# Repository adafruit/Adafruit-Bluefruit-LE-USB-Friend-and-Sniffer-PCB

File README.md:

## Adafruit Bluefruit LE USB Friend and Sniffer
&nbsp; <br />
Click to purchase from the Adafruit Shop:
- [Bluefruit LE Friend - Bluetooth Low Energy (BLE 4.0) - nRF51822 - v3.0](https://www.adafruit.com/product/2267)
- [Bluefruit LE Sniffer - Bluetooth Low Energy (BLE 4.0) - nRF51822 - Firmware Version 2](https://www.adafruit.com/product/2269)

The Bluefruit LE Friend is your new BLE BFF! This USB-to-BLE board makes it easy to get your computer talking to your BLE enabled phone or tablet using a standard serial/UART connection.

In it's simplest form, it works on the same principle as a common USB/Serial adapter (the FTDI Friend, for example!). Any data that you enter via your favorite terminal emulator on your development machine will be transferred over the air to the connected phone or tablet, and vice versa, as a basic 'UART' connection.

PCB files for the Bluefruit LE USB Friend and Sniffer
- https://www.adafruit.com/product/2267
- https://www.adafruit.com/product/2269

### License

Adafruit invests time and resources providing this open source design, please support Adafruit and open-source hardware by [purchasing products from Adafruit](https://www.adafruit.com)!

All text above must be included in any redistribution

Designed by Limor Fried/Ladyada for Adafruit Industries.
Creative Commons Attribution/Share-Alike, all text above must be included in any redistribution. 
See license.txt for additional information.

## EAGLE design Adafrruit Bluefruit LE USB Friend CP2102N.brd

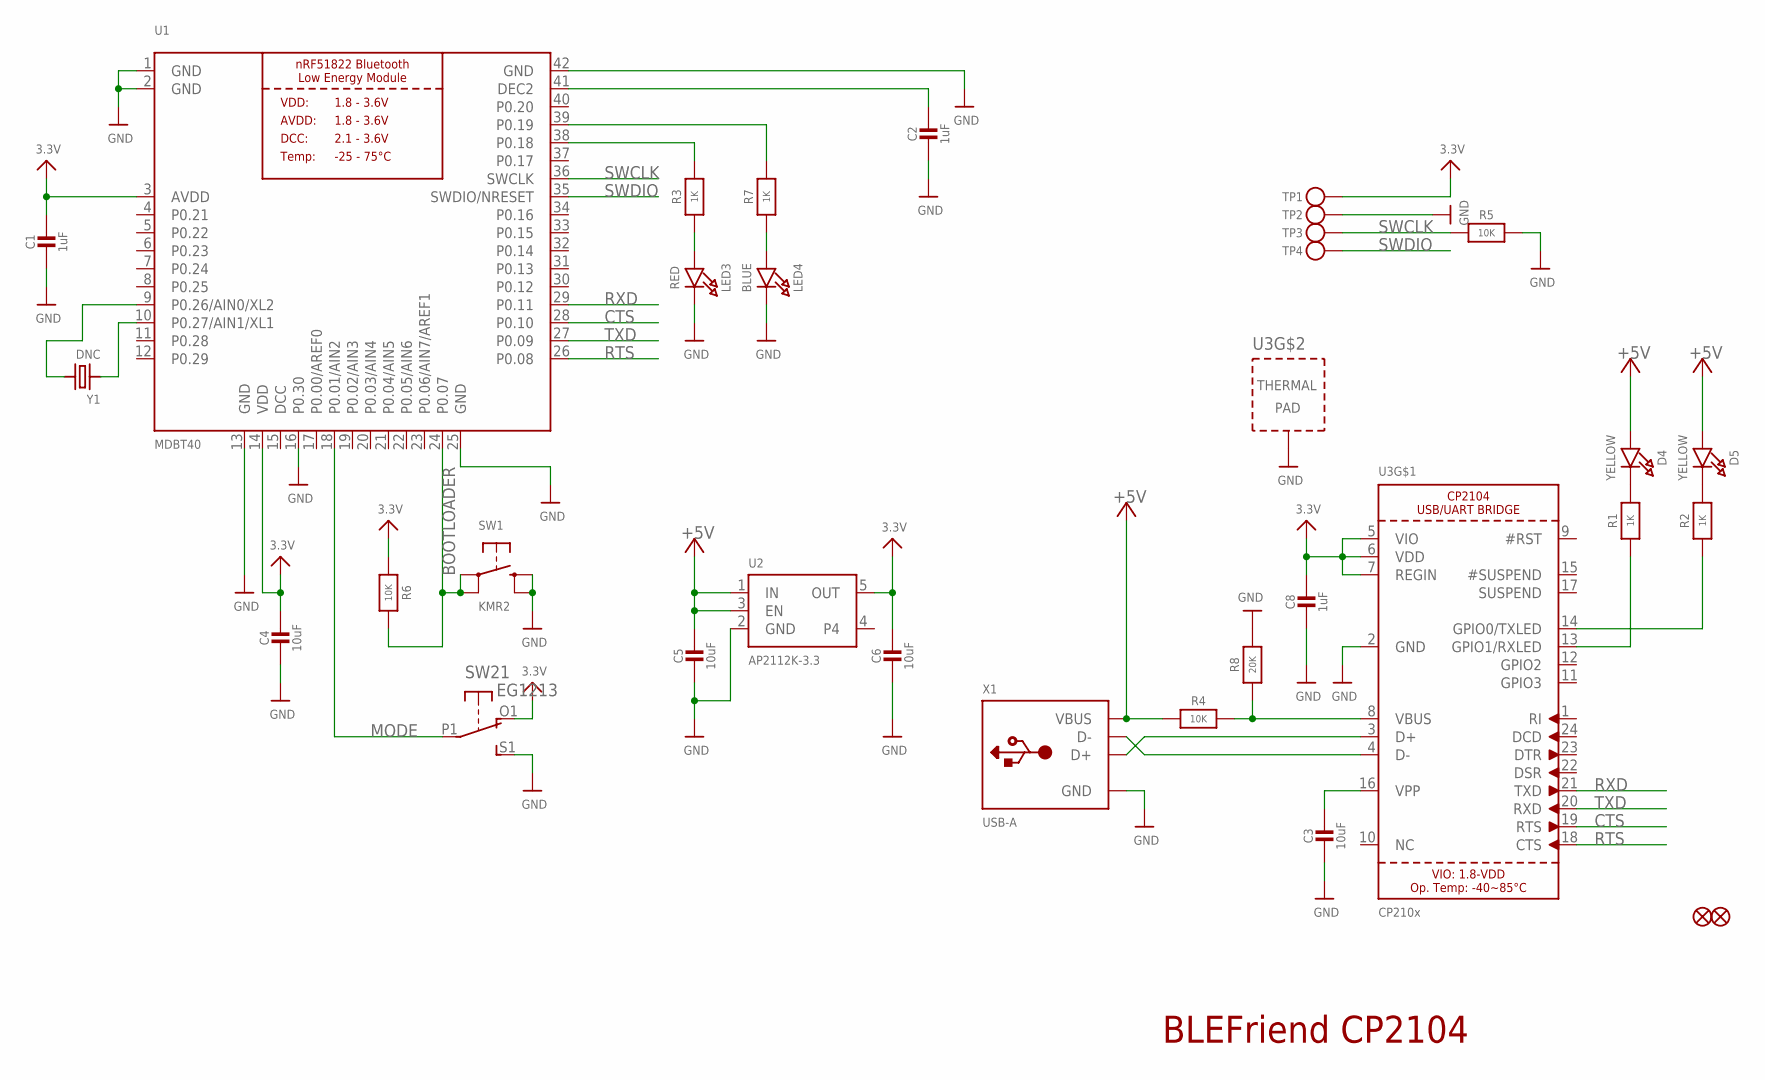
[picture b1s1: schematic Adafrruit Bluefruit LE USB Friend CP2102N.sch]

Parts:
C1, C2, C8: 1uF; 0603-NO
C3, C4, C5, C6: 10uF; 0805-NO
D4, D5: YELLOW; CHIPLED_0805_NOOUTLINE
FID1, FID2: FIDUCIAL_1MM
LED3: RED; CHIPLED_0805_NOOUTLINE
LED4: BLUE; CHIPLED_0805_NOOUTLINE
R1, R2, R3, R7: 1K; 0603-NO
R4, R5, R6: 10K; 0603-NO
R8: 20K; 0603-NO
SW1: KMR2; BTN_KMR2_4.6X2.8
SW2: EG1213; EG1390
TP1, TP2, TP3, TP4: TESTPOINTROUND2MM; TESTPOINT_ROUND_2MM
U1: MDBT40; BLE_MODULE_RAYTAC_MDBT40
U2: AP2112K-3.3; SOT23-5
U3: CP210x; QFN24_4MM_SMSC
X1: USB-A; USB_A-THM
Y1: DNC; CRYSTAL_CYL_2X6MM_SMT

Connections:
3.3V: C1.1, C4.1, C6.1, C8.1, R6.1, SW2.O1 (O), TP1.P$1, U1.3 (AVDD), U1.14 (VDD), U2.5 (OUT), U3.5 (VIO), U3.6 (VDD), U3.7 (REGIN)
+5V: C5.1, D4.A, D5.A, R4.1, U2.1 (IN), U2.3 (EN), X1.VBUS
BOOTLOADER: R6.2, SW1.A, SW1.A' (P1), U1.24 (P0.07)
CTS: U1.28 (P0.10), U3.19 (RTS)
DCC: U1.15 (DCC)
DEC2: C2.1, U1.41 (DEC2)
GND: C1.2, C2.2, C3.2, C4.2, C5.2, C6.2, C8.2, LED3.C, LED4.C, R5.2, R8.2, SW1.B (S), SW1.B' (S1), SW2.S1 (S), TP2.P$1, U1.1 (GND), U1.2 (GND), U1.13 (GND), U1.16 (P0.30), U1.25 (GND), U1.42 (GND), U2.2 (GND), U3.2 (GND), U3.THERM (TP), X1.GND
MODE: SW2.P1, U1.18 (P0.01/AIN2)
unnamed: U3.4 (D-), X1.D-
unnamed: D4.C, R1.2
unnamed: LED3.A, R3.1
unnamed: C3.1, U3.16 (VPP)
unnamed: R2.1, U3.14 (GPIO0/TXLED)
unnamed: D5.C, R2.2
unnamed: R4.2, R8.1, U3.8 (VBUS)
unnamed: U3.3 (D+), X1.D+
unnamed: R3.2, U1.38 (P0.18)
unnamed: R7.2, U1.39 (P0.19)
unnamed: LED4.A, R7.1
unnamed: U1.9 (P0.26/AIN0/XL2), Y1.2
unnamed: U1.10 (P0.27/AIN1/XL1), Y1.1
unnamed: R1.1, U3.13 (GPIO1/RXLED)
RTS: U1.26 (P0.08), U3.18 (CTS)
RXD: U1.29 (P0.11), U3.21 (TXD)
SWCLK: R5.1, TP3.P$1, U1.36 (SWCLK)
SWDIO: TP4.P$1, U1.35 (SWDIO/NRESET)
TXD: U1.27 (P0.09), U3.20 (RXD)

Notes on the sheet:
BLEFriend CP2104

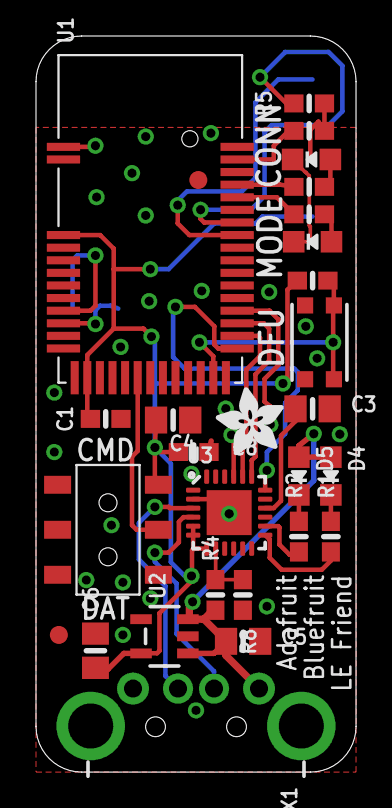
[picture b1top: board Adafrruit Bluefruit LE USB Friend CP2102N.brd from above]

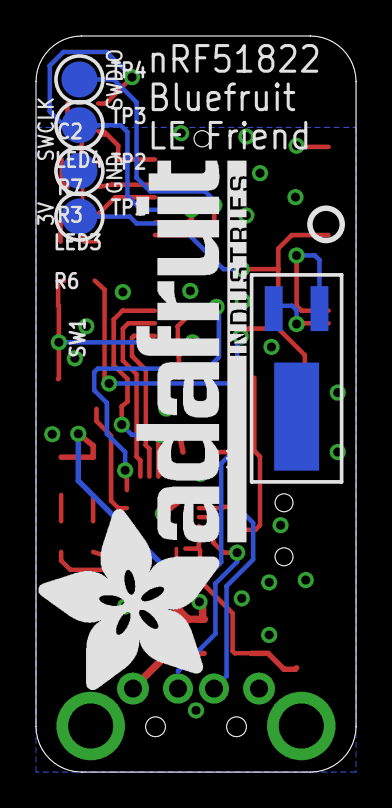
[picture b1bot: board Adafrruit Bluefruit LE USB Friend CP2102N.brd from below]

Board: 2 copper layers, 17.8 x 40.9 mm, 35 parts (7 on the bottom side), 26 nets.

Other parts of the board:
U$16: PCBFEAT-REV-040
U$22: ADAFRUIT_TEXT_30MM
U$31: ADAFRUIT_3.5MM

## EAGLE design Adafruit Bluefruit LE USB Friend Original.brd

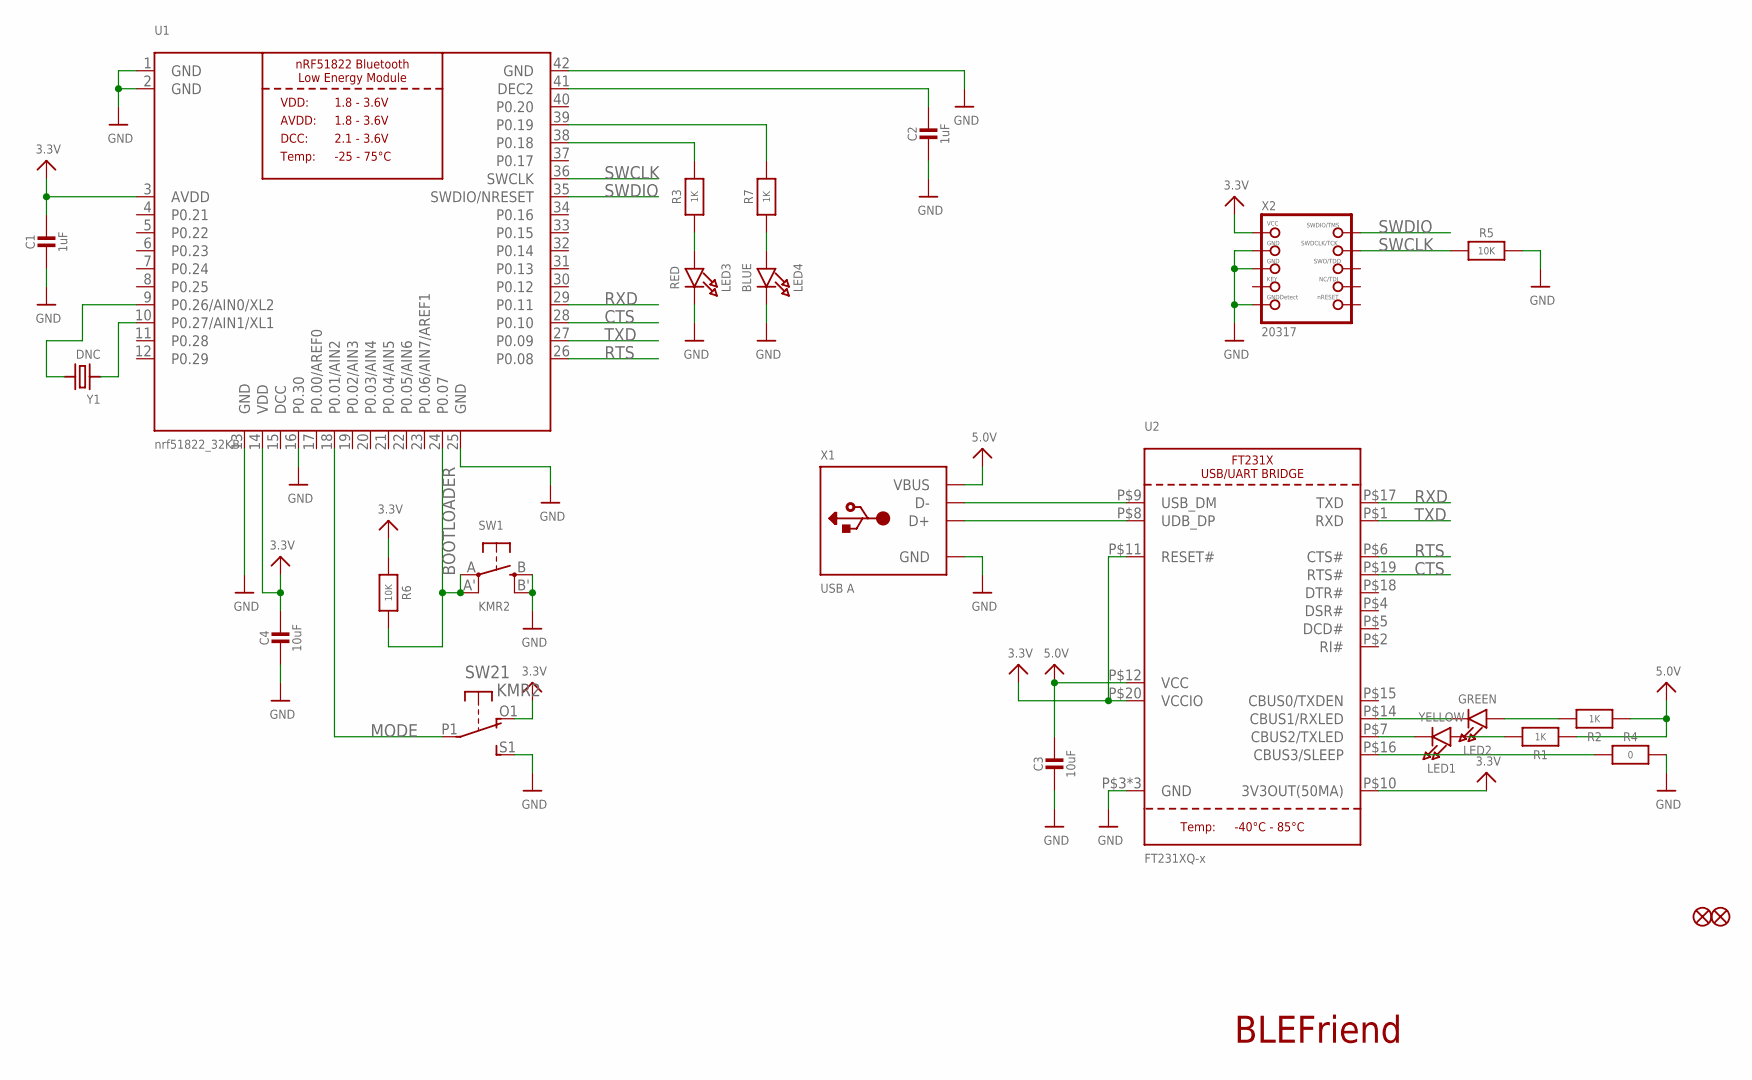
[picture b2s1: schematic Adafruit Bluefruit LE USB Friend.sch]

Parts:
C1, C2: 1uF; _0805MP
C3, C4: 10uF; _0805MP
FID1, FID2: FIDUCIAL""; FIDUCIAL_1MM
LED1: YELLOW; CHIPLED_0805_NOOUTLINE
LED2: GREEN; CHIPLED_0805_NOOUTLINE
LED3: RED; CHIPLED_0805_NOOUTLINE
LED4: BLUE; CHIPLED_0805_NOOUTLINE
R1, R2, R3, R7: 1K; _0805MP
R4: 0; _0805MP
R5, R6: 10K; _0805MP
SW1: KMR2; BTN_KMR2_4.6X2.8
SW2: KMR2; EG1390
U1: nrf51822_32KB; BLE_MODULE_RAYTAC_MDBT40
U2: FT231XQ-x; QFN20_4MM
X1: USB A; USB_A-THM
X2: 20317; 2X05_1.27MM_BOX_POSTS
Y1: DNC; CRYSTAL_CYL_2X6MM_SMT

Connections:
3.3V: C1.1, C4.1, R6.1, SW2.O1 (O), U1.3 (AVDD), U1.14 (VDD), U2.P$10 (3V3OUT(50MA)), U2.P$11 (RESET#), U2.P$20 (VCCIO), X2.1 (VCC)
5.0V: C3.1, R1.1, R2.1, U2.P$12 (VCC), X1.VBUS
BOOTLOADER: R6.2, SW1.A, SW1.A' (P1), U1.24 (P0.07)
CTS: U1.28 (P0.10), U2.P$19 (RTS#)
DCC: U1.15 (DCC)
GND: C1.2, C2.2, C3.2, C4.2, LED3.C, LED4.C, R4.2, R5.2, SW1.B (S), SW1.B' (S1), SW2.S1 (S), U1.1 (GND), U1.2 (GND), U1.13 (GND), U1.16 (P0.30), U1.25 (GND), U1.42 (GND), U2.P$3 (GND), U2.P$13 (GND), U2.P$21 (GND), X1.GND, X2.3 (GND), X2.5 (GND), X2.9 (GNDDETECT)
MODE: SW2.P1, U1.18 (P0.01/AIN2)
unnamed: LED2.A, R2.2
unnamed: C2.1, U1.41 (DEC2)
unnamed: LED3.A, R3.1
unnamed: LED1.A, R1.2
unnamed: LED1.C, U2.P$7 (CBUS2/TXLED)
unnamed: LED2.C, U2.P$14 (CBUS1/RXLED)
unnamed: R4.1, U2.P$16 (CBUS3/SLEEP)
unnamed: U2.P$8 (UDB_DP), X1.D+
unnamed: U2.P$9 (USB_DM), X1.D-
unnamed: R3.2, U1.38 (P0.18)
unnamed: R7.2, U1.39 (P0.19)
unnamed: LED4.A, R7.1
unnamed: U1.9 (P0.26/AIN0/XL2), Y1.2
unnamed: U1.10 (P0.27/AIN1/XL1), Y1.1
RTS: U1.26 (P0.08), U2.P$6 (CTS#)
RXD: U1.29 (P0.11), U2.P$17 (TXD)
SWCLK: R5.1, U1.36 (SWCLK), X2.4 (SWDCLK)
SWDIO: U1.35 (SWDIO/NRESET), X2.2 (SWDIO)
TXD: U1.27 (P0.09), U2.P$1 (RXD)

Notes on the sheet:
BLEFriend

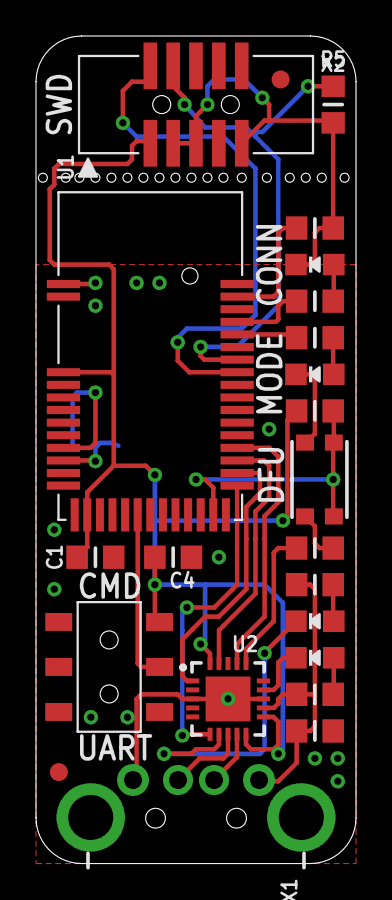
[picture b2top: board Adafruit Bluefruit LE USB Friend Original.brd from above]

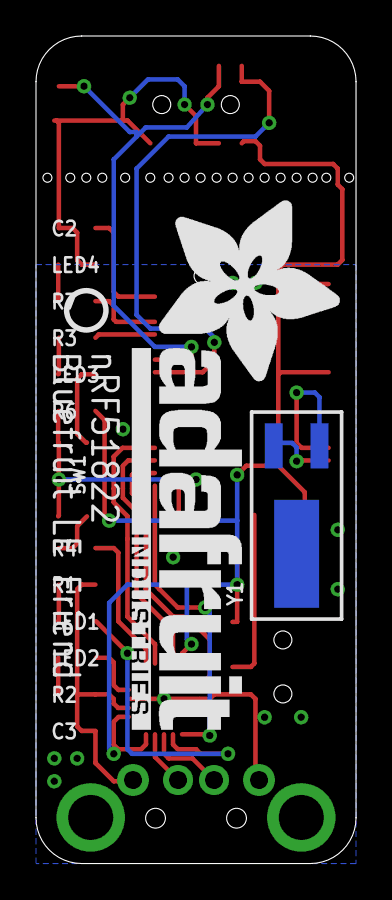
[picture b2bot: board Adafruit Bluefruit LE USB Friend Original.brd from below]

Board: 2 copper layers, 17.8 x 46.0 mm, 26 parts (3 on the bottom side), 25 nets.

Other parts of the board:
U$22: ADAFRUIT_TEXT_30MM
U$27: PCBFEAT-REV-056

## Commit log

2016-07-15 twofer
2021-07-14 Rename Adafruit Bluefruit LE USB Friend.brd to Adafruit Bluefruit LE USB Friend Original.brd
2021-07-14 Rename Adafruit Bluefruit LE USB Friend Original.brd to Adafruit Bluefruit LE USB Friend.brd
2021-07-14 Add latest board files.

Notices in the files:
parts and their libraries:
microbuilder: This work is placed in the public domain, and may be freely used for commercial and non-commercial work with the following conditions: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
